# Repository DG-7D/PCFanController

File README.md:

# PCファン制御器

## 機能

- USB PDから12 V要求しファンに給電
- 回転数の低遅延表示
- PWM指令値の調整
- ファン電源のON/OFF

## 操作

- 4ピンPCファン、12V出力対応のUSB PD電源を接続
- 始動時は停止状態、+を押すと30%で始動

| ボタン | 操作 |
| ----: | :---- |
| DISP | 表示切替 (回転数表示→指令値表示→消灯→(ループ)) |
| + | 指令値増加、停止時に押すと始動 |
| - | 指令値減少、0%のとき押すと停止 |

## PCファンの動作

4ピンのPCファンの場合、PCやこの制御器が指令するのは最大回転数に対する割合であり、PWMのデューティー比の形で送信され、回転数の制御はファン側で行われる。30%以上ではおおむね線形に変化するようにファン側で制御される。30%未満での挙動はファンにより異なり、最低の回転数を維持するものが多く、0%では停止したりしなかったりする。

0%で停止しないファンであっても、この制御器の停止状態では通電自体を切るので停止する。

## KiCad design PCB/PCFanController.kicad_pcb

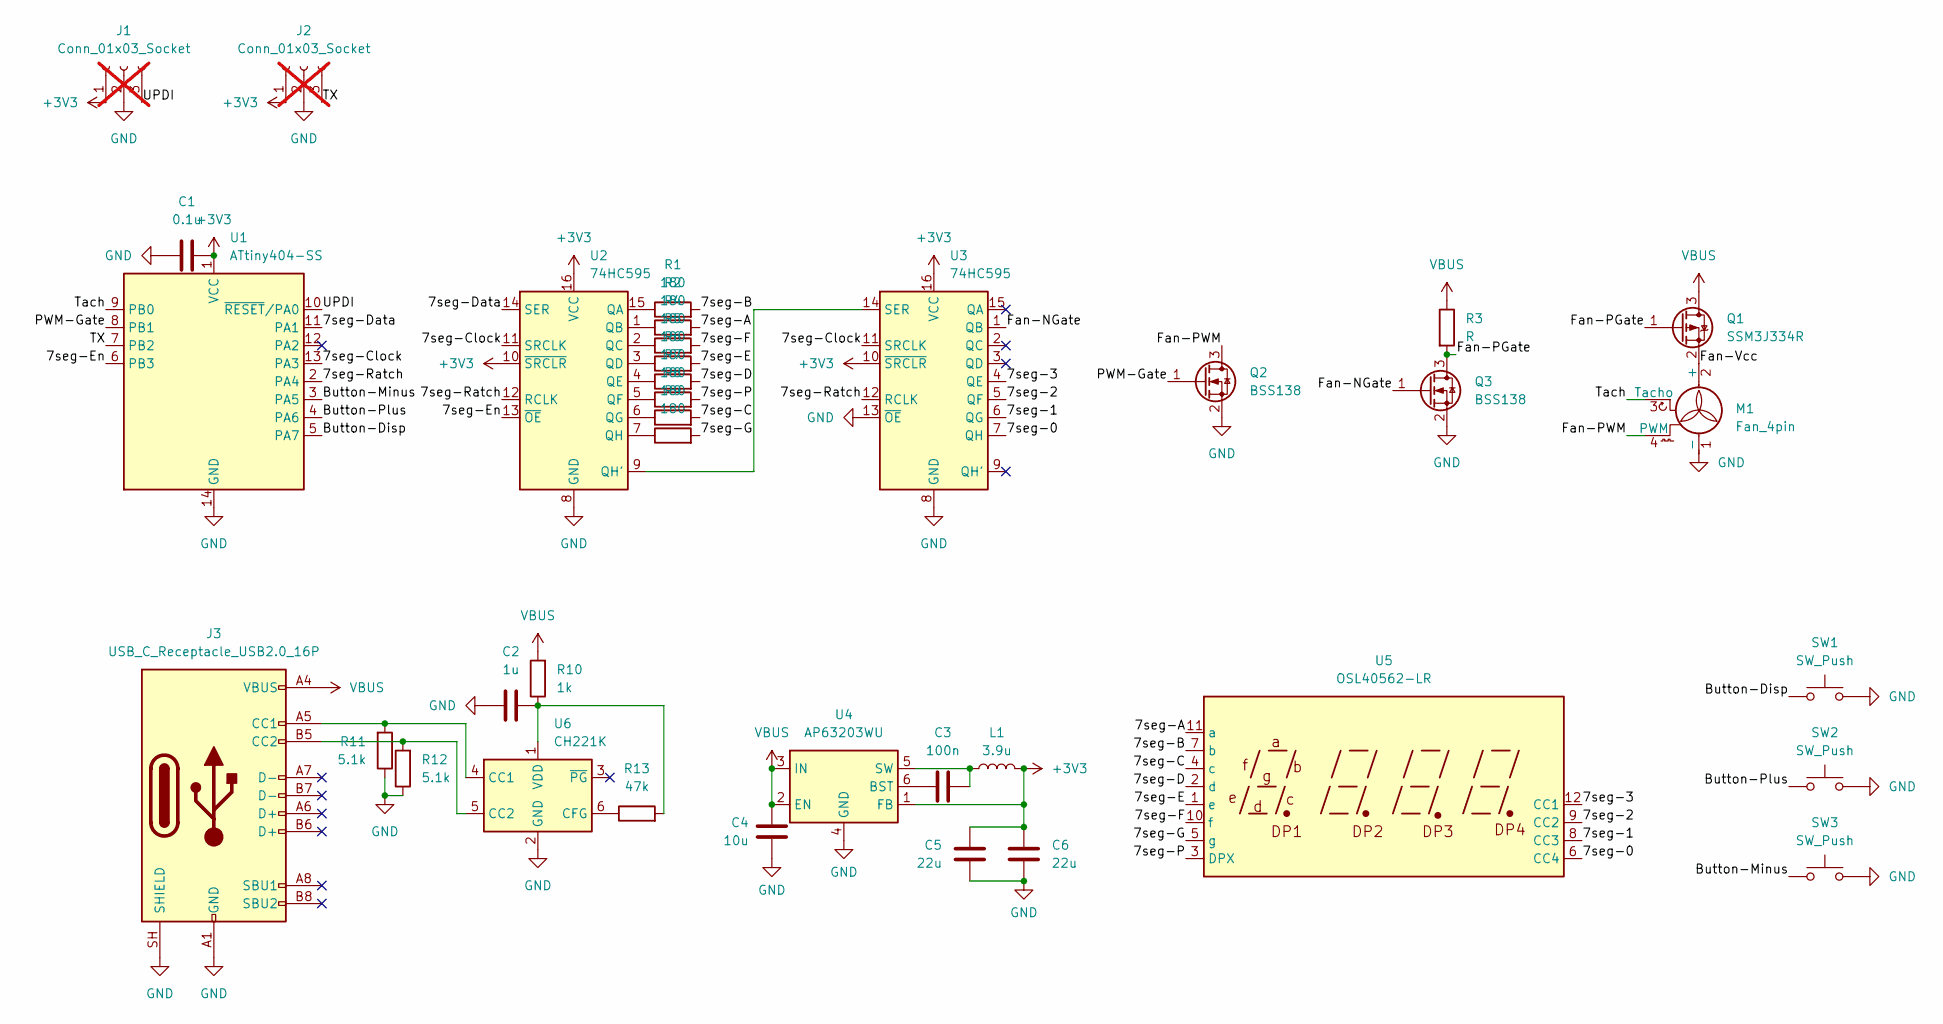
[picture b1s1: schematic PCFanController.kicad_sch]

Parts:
C1: 0.1u; C_0603_1608Metric
C2: 1u; C_0603_1608Metric
C3: 100n; C_0603_1608Metric
C4: 10u; C_0603_1608Metric
C5, C6: 22u; C_0603_1608Metric
J1, J2: Conn_01x03_Socket; PinSocket_1x03_P2.54mm_Vertical; not fitted
J3: USB_C_Receptacle_USB2.0_16P; USB_C_Receptacle_GCT_USB4105-xx-A_16P_TopMnt_Horizontal
L1: 3.9u; L_1210_3225Metric
M1: Fan_4pin; FanPinHeader_1x04_P2.54mm_Vertical
Q1: SSM3J334R; SOT-23
Q2, Q3: BSS138; SOT-23
R1, R2, R4, R5, R6, R7, R8, R9: 180; R_0603_1608Metric
R3: R; SOT-23
R10: 1k; R_0603_1608Metric
R11, R12: 5.1k; R_0603_1608Metric
R13: 47k; R_0603_1608Metric
SW1, SW2, SW3: SW_Push; R_Axial_DIN0204_L3.6mm_D1.6mm_P5.08mm_Horizontal
U1: ATtiny404-SS; SOIC-14_3.9x8.7mm_P1.27mm
U2, U3: 74HC595; TSSOP-16_4.4x5mm_P0.65mm
U4: AP63203WU; TSOT-23-6
U5: OSL40562-LR; CA56-12EWA
U6: CH221K; SOT-23-6

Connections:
+3V3: C1.2, C5.2, C6.2, J1.1, J2.1, L1.2, U1.1 (VCC), U2.10 (~SRCLR), U2.16 (VCC), U3.10 (~SRCLR), U3.16 (VCC), U4.1 (FB)
/7seg-0: U3.7 (QH), U5.6 (CC4)
/7seg-1: U3.6 (QG), U5.8 (CC3)
/7seg-2: U3.5 (QF), U5.9 (CC2)
/7seg-3: U3.4 (QE), U5.12 (CC1)
/7seg-A: R2.2, U5.11 (a)
/7seg-B: R1.2, U5.7 (b)
/7seg-C: R8.2, U5.4 (c)
/7seg-Clock: U1.13 (PA3), U2.11 (SRCLK), U3.11 (SRCLK)
/7seg-D: R6.2, U5.2 (d)
/7seg-Data: U1.11 (PA1), U2.14 (SER)
/7seg-E: R5.2, U5.1 (e)
/7seg-En: U1.6 (PB3), U2.13 (~OE)
/7seg-F: R4.2, U5.10 (f)
/7seg-G: R9.2, U5.5 (g)
/7seg-P: R7.2, U5.3 (DPX)
/7seg-Ratch: U1.2 (PA4), U2.12 (RCLK), U3.12 (RCLK)
/Button-Disp: SW1.1, U1.5 (PA7)
/Button-Minus: SW3.1, U1.3 (PA5)
/Button-Plus: SW2.1, U1.4 (PA6)
/Fan-NGate: Q3.1 (G), U3.1 (QB)
/Fan-PGate: Q1.1 (G), Q3.3 (D), R3.2
/Fan-PWM: M1.4 (PWM), Q2.3 (D)
/Fan-Vcc: M1.2 (+), Q1.2 (S)
/PWM-Gate: Q2.1 (G), U1.8 (PB1)
/TX: J2.3, U1.7 (PB2)
/Tach: M1.3 (Tacho), U1.9 (PB0)
/UPDI: J1.3, U1.10 (~RESET/PA0)
GND: C1.1, C2.1, C4.2, C5.1, C6.1, J1.2, J2.2, J3.A1 (GND), J3.A12 (GND), J3.B1 (GND), J3.B12 (GND), J3.SH (SHIELD), M1.1 (-), Q2.2 (S), Q3.2 (S), R11.1, R12.1, SW1.2, SW2.2, SW3.2, U1.14 (GND), U2.8 (GND), U3.8 (GND), U3.13 (~OE), U4.4 (GND), U6.2 (GND)
unnamed: J3.A5 (CC1), R11.2, U6.4 (CC1)
unnamed: J3.B5 (CC2), R12.2, U6.5 (CC2)
unnamed: R1.1, U2.15 (QA)
unnamed: R2.1, U2.1 (QB)
unnamed: R4.1, U2.2 (QC)
unnamed: R5.1, U2.3 (QD)
unnamed: R6.1, U2.4 (QE)
unnamed: R7.1, U2.5 (QF)
unnamed: R8.1, U2.6 (QG)
unnamed: U2.9 (QH'), U3.14 (SER)
unnamed: R9.1, U2.7 (QH)
unnamed: C3.1, U4.6 (BST)
unnamed: C3.2, L1.1, U4.5 (SW)
unnamed: R13.1, U6.6 (CFG)
unnamed: C2.2, R10.1, R13.2, U6.1 (VDD)
VBUS: C4.1, J3.A4 (VBUS), J3.A9 (VBUS), J3.B4 (VBUS), J3.B9 (VBUS), Q1.3 (D), R3.1, R10.2, U4.2 (EN), U4.3 (IN)

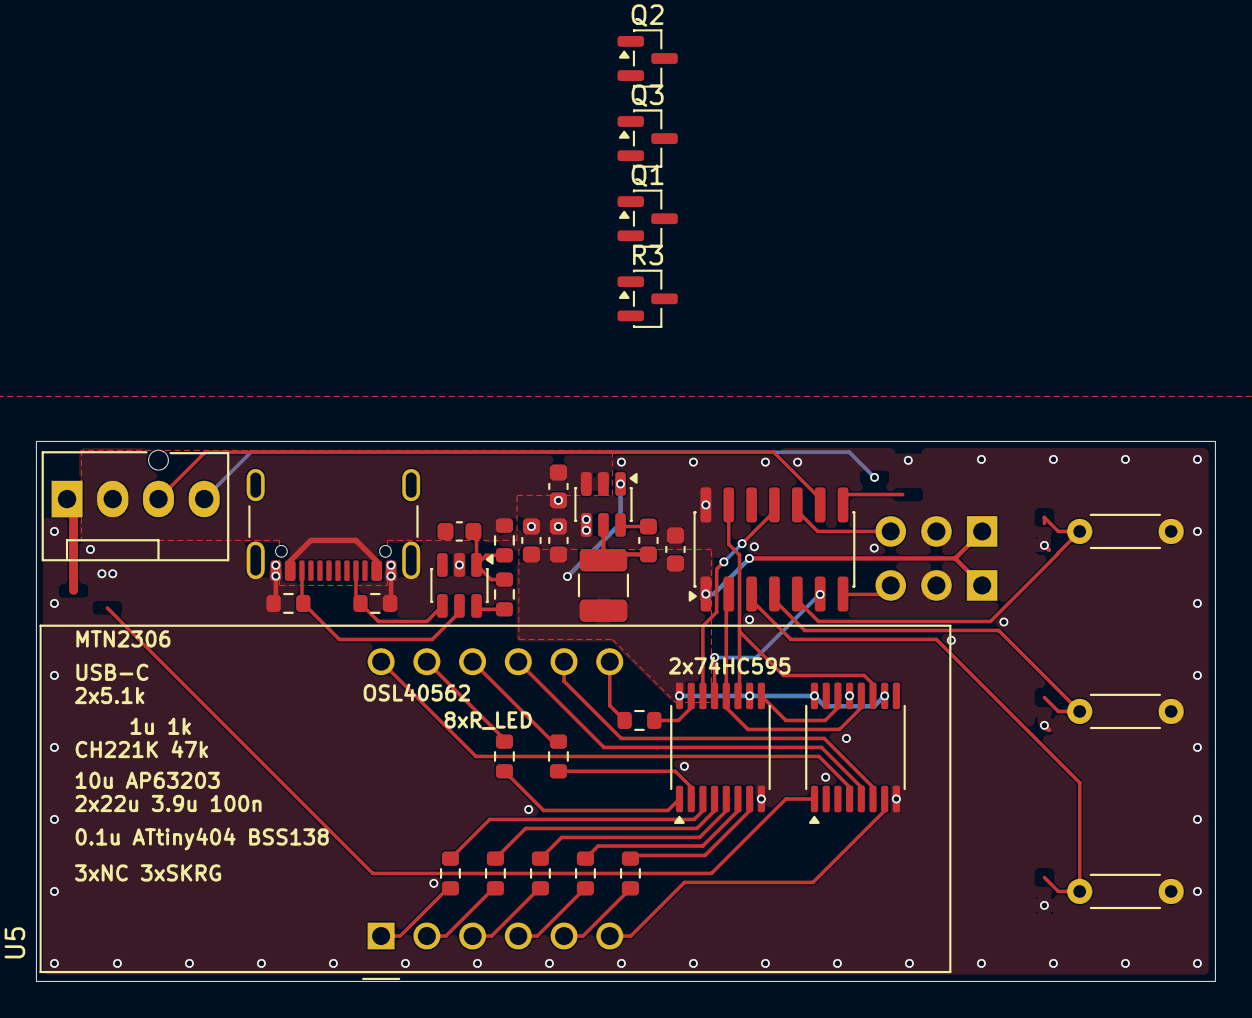
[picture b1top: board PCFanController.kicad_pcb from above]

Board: 2 copper layers, 65.5 x 30.0 mm, 36 parts (0 on the bottom side), 45 nets.
